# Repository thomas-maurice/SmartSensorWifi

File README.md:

# Smart Sensor WiFi
## General information

 * Developpement status : *work in progress*
 * Project version   : 0.1 alpha

Project led by:

 * Thomas Maurice <Thomas.Maurice@polytech-lille.net>
 * Benoit Maliar  <Benoit.Maliar@polytech-lille.net>

## About the project
This project aims to build a network of sensors which can easily be
deployed into any building to monitor it. The sensors would be able to
monitor temperature, light, moist, presence and so on and send everything
to a centralized database into which data will be stored and processed.

We can easily imagine which use can be done of this kind of sensor networks
in the field of energy-efficient building.

For now, this project is part of a student project led by Polytech'Lille,
a french school of engineering.

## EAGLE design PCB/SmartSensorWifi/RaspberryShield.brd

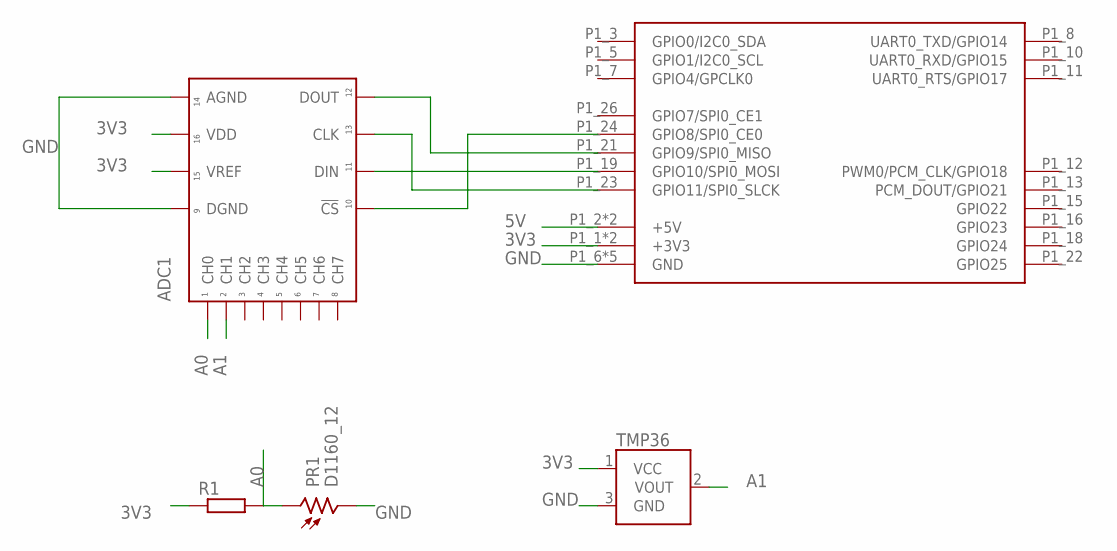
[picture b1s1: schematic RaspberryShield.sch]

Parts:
ADC1: 21298EDIP; DIP16
PR1: D1160_12; D11XX
R1: R-EU_0207/7; 0207/7
TMP36: TMP36GT9; TO-92
U$1: RPI-B-V1SHIELD; RPI-B-V1-SHIELD

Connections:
3V3: ADC1.P$15 (VREF), ADC1.P$16 (VDD), R1.1, TMP36.1 (VCC), U$1.P1_1 (+3V3), U$1.P1_17 (+3V3)
5V: U$1.P1_2 (+5V), U$1.P1_4 (+5V)
A0: ADC1.P$1 (CH0), PR1.1, R1.2
A1: ADC1.P$2 (CH1), TMP36.2 (VOUT)
GND: ADC1.P$9 (DGND), ADC1.P$14 (AGND), PR1.2, TMP36.3 (GND), U$1.P1_6 (GND), U$1.P1_9 (GND), U$1.P1_14 (GND), U$1.P1_20 (GND), U$1.P1_25 (GND)
unnamed: ADC1.P$12 (DOUT), U$1.P1_21 (GPIO9/SPI0_MISO)
unnamed: ADC1.P$11 (DIN), U$1.P1_19 (GPIO10/SPI0_MOSI)
unnamed: ADC1.P$13 (CLK), U$1.P1_23 (GPIO11/SPI0_SLCK)
unnamed: ADC1.P$10 (!CS), U$1.P1_24 (GPIO8/SPI0_CE0)

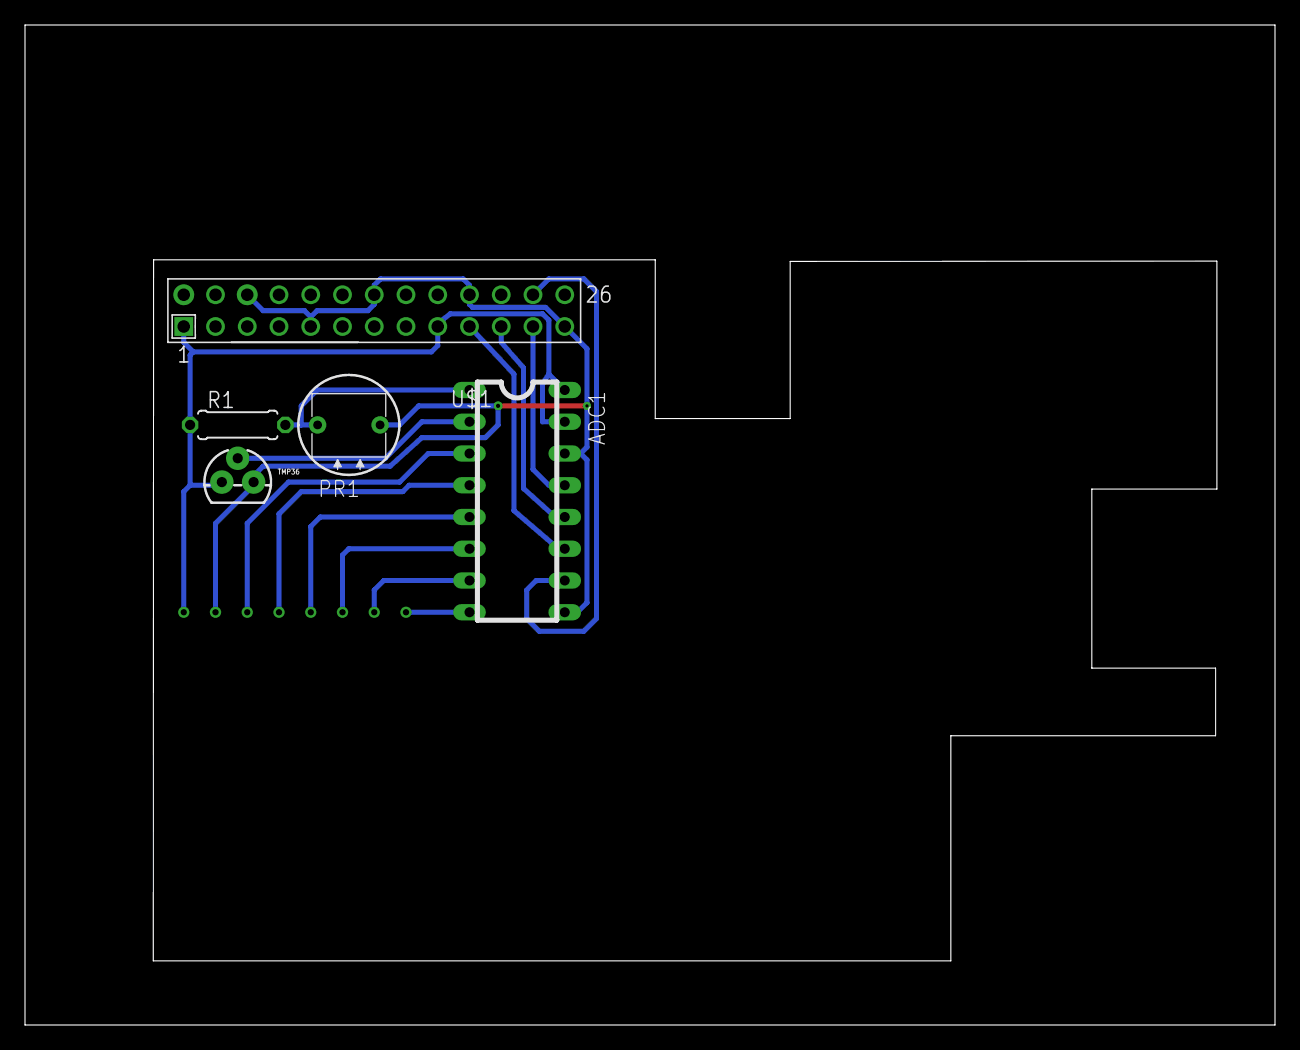
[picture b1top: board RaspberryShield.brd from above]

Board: 2 copper layers, 100.0 x 80.0 mm, 5 parts (0 on the bottom side), 9 nets.

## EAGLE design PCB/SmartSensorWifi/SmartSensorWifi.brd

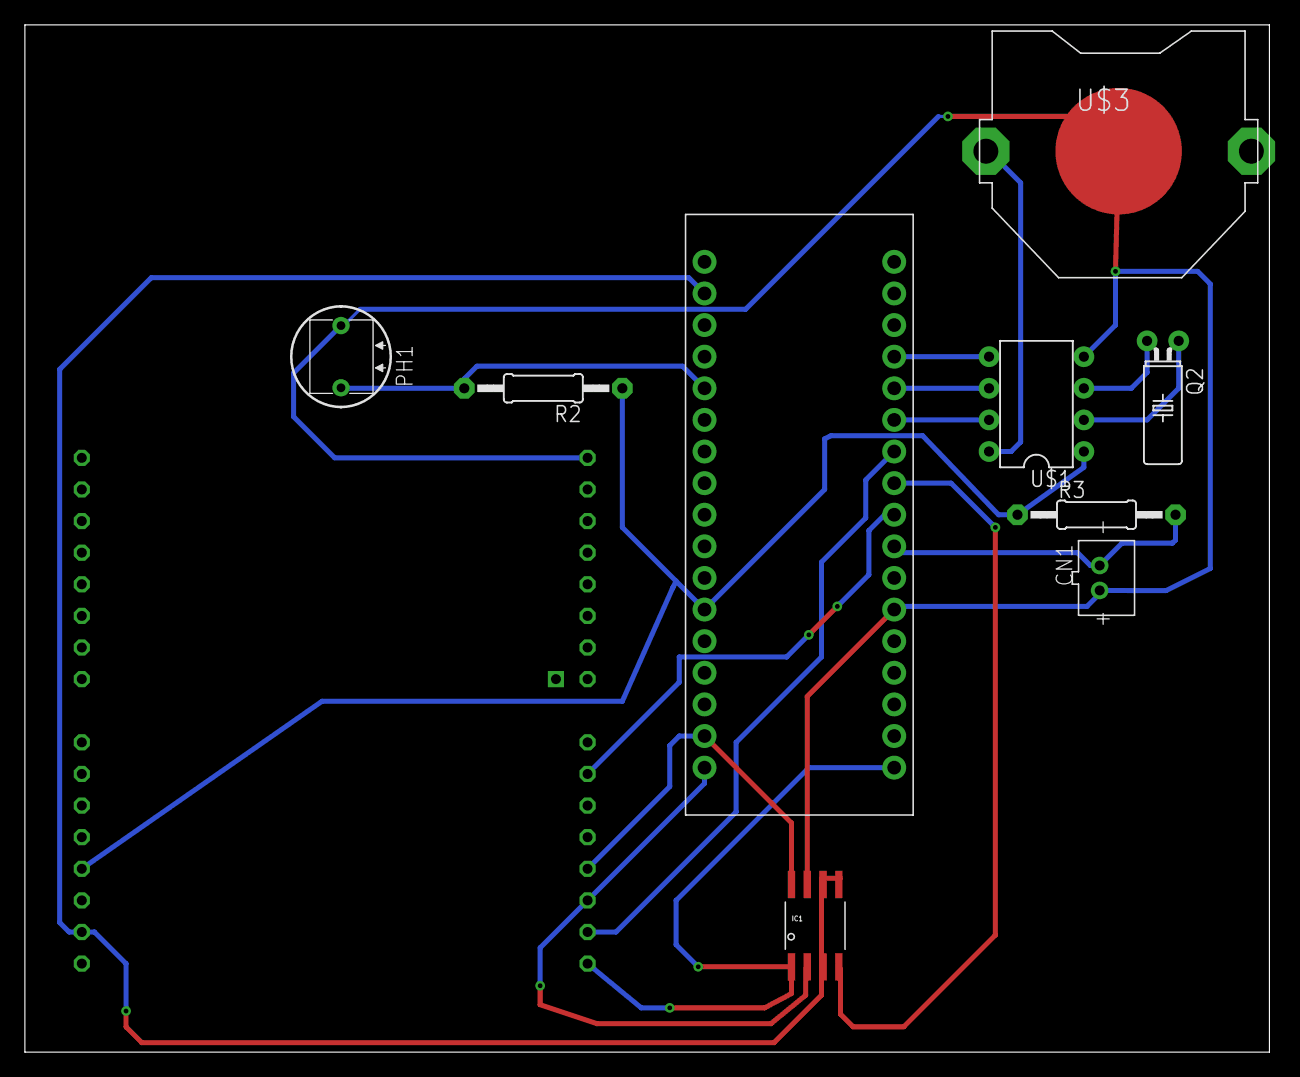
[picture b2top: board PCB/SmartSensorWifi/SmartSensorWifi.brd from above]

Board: 2 copper layers, 100.0 x 82.5 mm, 10 parts (1 on the bottom side), 18 nets.

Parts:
CN1: JST-PH-2-THM
IC1: AT45DB-S; SOIC8_208MIL
PH1: D1160_12; D11XX
Q2: TC38H
R2: 220; 0207/12
R3: 0207/12
U$1: DS1302; DIL08-ROUND
U$2: ARDUINOMICRO
U$3: CR2032-THRU
U$4: WIZFISTACKED; WIZFI210STACKABLE

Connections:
3V3: IC1.3, U$2.P$33, U$4.VIN3V3
5V: R2.1, R3.1, U$1.1, U$2.P$23, U$4.VDDIO
A1: PH1.1, R2.2, U$2.P$30
CS_FLASH: IC1.4, U$2.P$8
CS_WIFI: U$2.P$7, U$4.SPI_CS
GND: CN1.1, IC1.7, U$1.4, U$2.P$21, U$3.-
MISO: IC1.8, U$2.P$19, U$4.SPI_MISO
MOSI: IC1.1, U$2.P$17, U$4.SPI_MOSI
unnamed: U$1.5, U$2.P$4
unnamed: Q2.2, U$1.3
unnamed: Q2.1, U$1.2
unnamed: U$1.7, U$2.P$6
unnamed: U$1.6, U$2.P$5
unnamed: U$1.8, U$3.+1
PSHBTN: CN1.2, R3.2, U$2.P$10
S$1: PH1.2, U$4.GND
SCK: IC1.2, U$2.P$18, U$4.SPI_CLK
WIFI_HOSTWAKEUP: U$2.P$9, U$4.GPIO19

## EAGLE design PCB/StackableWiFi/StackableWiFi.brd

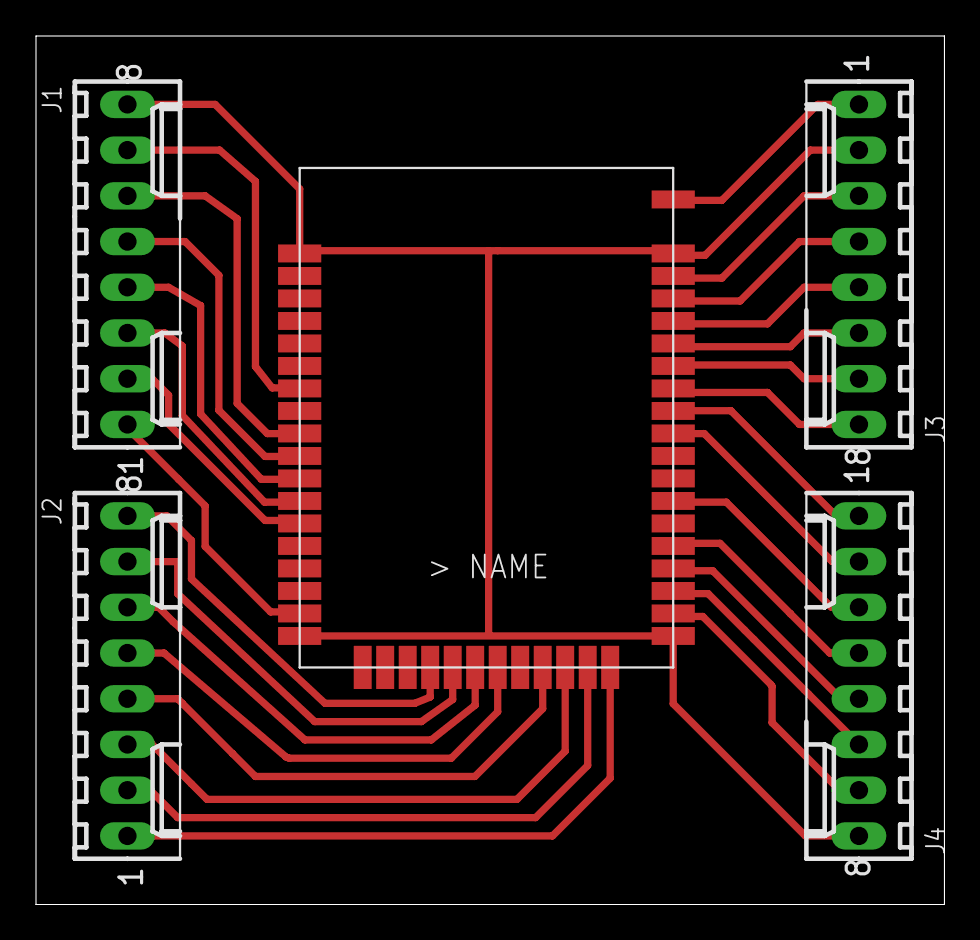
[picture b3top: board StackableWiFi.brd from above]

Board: 2 copper layers, 50.5 x 48.2 mm, 5 parts (0 on the bottom side), 32 nets.

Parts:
J1, J2, J3, J4: 22-27-2081-08; 6410-08
WIFI1: WIZFI210

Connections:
unnamed: J1.8, WIFI1.1
unnamed: J1.7, WIFI1.7
unnamed: J1.6, WIFI1.9
unnamed: J1.5, WIFI1.10
unnamed: J1.4, WIFI1.11
unnamed: J1.3, WIFI1.12
unnamed: J1.2, WIFI1.13
unnamed: J1.1, WIFI1.17
unnamed: J4.8, WIFI1.18, WIFI1.31
unnamed: J2.8, WIFI1.22
unnamed: J2.7, WIFI1.23
unnamed: J2.6, WIFI1.24
unnamed: J2.5, WIFI1.25
unnamed: J2.4, WIFI1.27
unnamed: J2.3, WIFI1.28
unnamed: J2.2, WIFI1.29
unnamed: J2.1, WIFI1.30
unnamed: J4.7, WIFI1.32
unnamed: J4.6, WIFI1.33
unnamed: J4.5, WIFI1.34
unnamed: J4.4, WIFI1.35
unnamed: J4.3, WIFI1.37
unnamed: J4.2, WIFI1.40
unnamed: J4.1, WIFI1.41
unnamed: J3.8, WIFI1.42
unnamed: J3.7, WIFI1.43
unnamed: J3.6, WIFI1.44
unnamed: J3.5, WIFI1.45
unnamed: J3.4, WIFI1.46
unnamed: J3.3, WIFI1.47
unnamed: J3.2, WIFI1.48
unnamed: J3.1, WIFI1.49

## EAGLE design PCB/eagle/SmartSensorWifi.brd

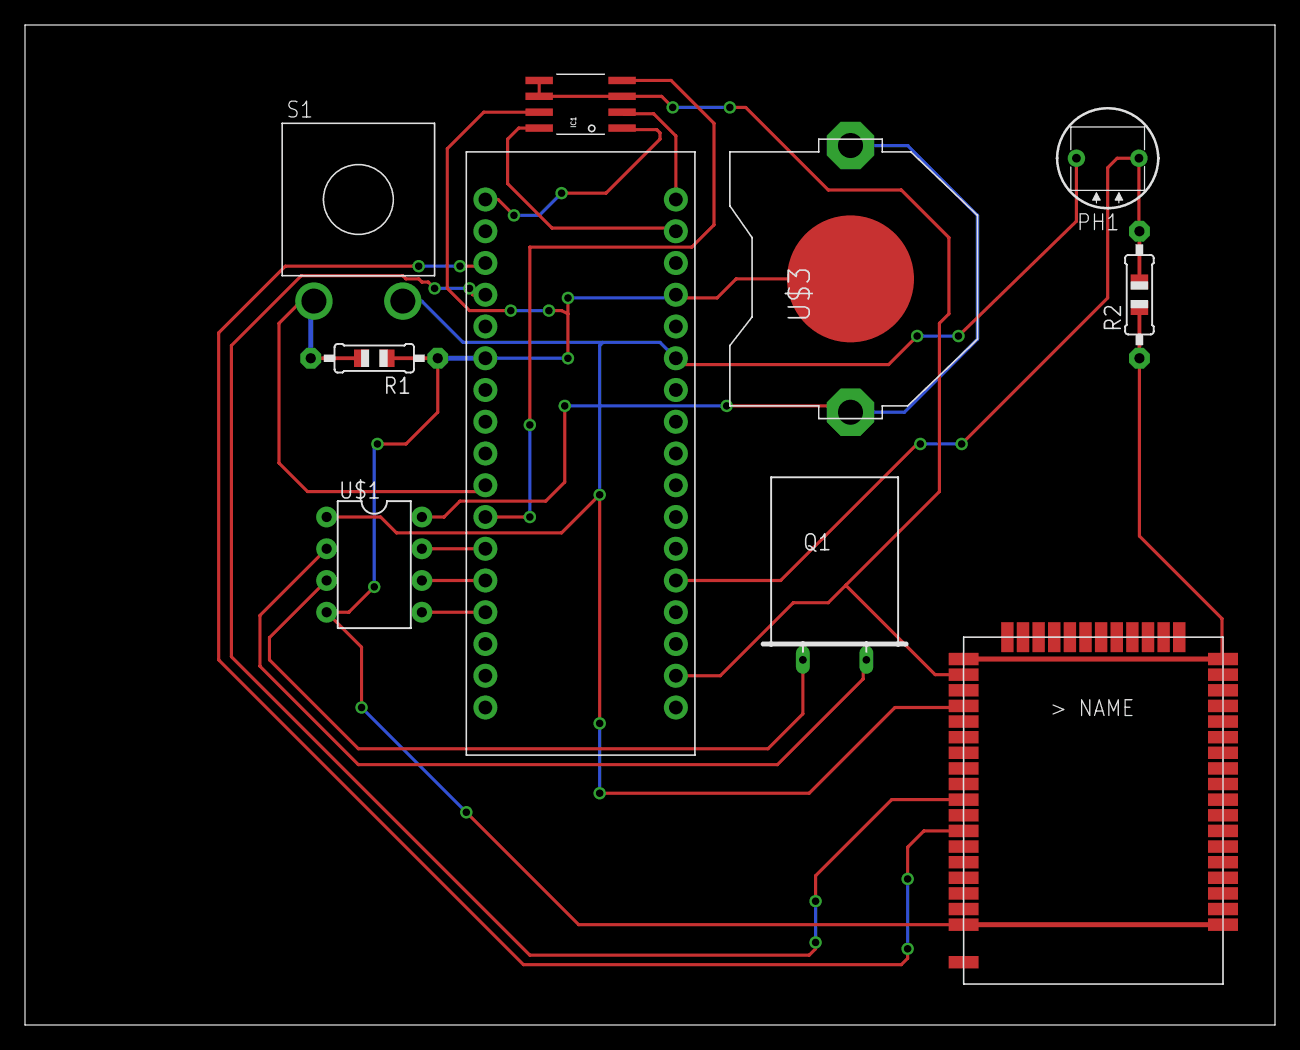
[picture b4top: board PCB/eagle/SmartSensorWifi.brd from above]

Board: 2 copper layers, 100.0 x 80.0 mm, 10 parts (0 on the bottom side), 17 nets.

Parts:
IC1: AT45DB-S; SOIC8_208MIL
PH1: D1160_12; D11XX
Q1: Q
R1, R2: 0805-THM
S1: SPST; JUDCOSPST
U$1: DS1302; DIL08-ROUND
U$2: ARDUINOMICRO
U$3: CR2032-THRU
WIFI1: WIZFI210

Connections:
GND: IC1.7, R1.1, R2.1, U$1.4, U$2.P$12, U$2.P$21, U$3.-, WIFI1.1, WIFI1.18, WIFI1.31, WIFI1.48
unnamed: U$1.5, U$2.P$4
unnamed: Q1.1, U$1.3
unnamed: Q1.2, U$1.2
unnamed: U$1.7, U$2.P$6
unnamed: U$1.6, U$2.P$5
unnamed: IC1.8, U$2.P$19
unnamed: IC1.2, U$2.P$18
unnamed: IC1.1, U$2.P$17
unnamed: IC1.3, IC1.5, IC1.6, U$2.P$33, WIFI1.32
unnamed: U$1.8, U$3.+1, U$3.+2
unnamed: IC1.4, U$2.P$7
unnamed: R1.2, S1.T, U$2.P$8
unnamed: U$2.P$14, WIFI1.40
unnamed: U$2.P$15, WIFI1.42
unnamed: PH1.2, R2.2, U$2.P$30
VCC: PH1.1, S1.P, U$1.1, U$2.P$23, WIFI1.34

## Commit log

2014-02-02 Creating the repo + adding doc
2014-02-02 Added COPYING
2014-02-02 Added README.md & AUTHORS
2014-02-02 Added compilation script for the documentation
2014-02-03 Ajout des propositions de technologies
2014-02-03 Created README.md
2014-02-06 Added the Arduino part of the project
2014-02-06 Added utility script for the serial port read
2014-02-06 Fixed upload speed to make it work on arduino nano
2014-02-07 Added the eeprom management files + comments and license info
2014-02-08 Added macros
2014-02-08 comments
2014-02-08 Added a README for the util section
2014-02-08 Fixed crash in ASCII mode if non utf8 chars
2014-02-17 Added a lot of documentation
2014-02-18 Added the DS1302 driver
2014-02-19 fixed comments
2014-02-21 Web
    Add the Web folder
2014-02-21 Web
    Add ALL the Web directory
2014-02-28 Added Doxyfile for Doxygen documentation
2014-02-28 Added a README.md
2014-02-28 Enhanced README
2014-02-28 Added PCB folder
2014-02-28 Updated board
2014-02-28 Added auto detection for serial ports
2014-03-05 Added set time/date capabilities
2014-03-06 Updated the eagle files
2014-03-13 Added json test script
2014-03-13 wow much doc
2014-03-13 Updated the PCB/BRD files
2014-03-15 Added the Raspberry SPI soft
2014-03-17 Test Json
2014-03-18 Fonctionnal website
    Adding session (using cookie), captors' adding.
    Partially implemented : delete captors.
2014-03-19 Reconstruction du makefile
2014-03-19 Wow, such captors
    Update index, search, add, del.
2014-03-19 Added wizfi
2014-03-19 Fix search.php
2014-03-24 Search Working !
2014-03-31 Changing Json to Post (recup.php)
2014-04-01 Ability to send post request + report sekeleton
2014-04-02 Adding new functions to administration panel
2014-04-03 Added configurator and the ability to configure the sensor via serial
2014-04-04 Enhanced configurator
2014-04-04 Added doc
2014-04-04 Configurator now works wirelessly
2014-04-07 Update Git with FTP files
2014-04-07 added loads of docs in the microcontroller part
2014-04-07 Start commenting properly yeah !
2014-04-07 Added at commands doc
2014-04-07 THIS IS COMMENTS !
2014-04-07 Adding chart.js in order to make graph
2014-04-07 Commenting the graph's file
2014-04-07 Requests ordered by timestamp
2014-04-08 Created the main files for the report
2014-04-09 Updated configurator
2014-04-09 Fix missing graph when same values
2014-04-09 Fixed master key issue
2014-04-09 added configurator doc
2014-04-10 updated report
2014-04-10 Added accomplishment, sensor, software
2014-04-10 Added accomplishment, sensor, HARDWARE
2014-04-10 added stuff
2014-04-10 Added stuff and skel
2014-04-10 addedshitlolwowsuch
2014-04-10 more shit
2014-04-11 Correction coquille
2014-04-12 Updated doc
2014-04-12 edited configurator
2014-04-12 added report
2014-04-12 enhanced report
2014-04-12 enhanced doc
2014-04-12 Fuck this shit UTF8
2014-04-12 Fix ?
2014-04-12 Acheviements completed !
2014-04-13 Web Completed !
2014-04-13 Conclusion added
2014-04-13 Fixed typos
2014-04-14 Enhanced RaspberrySpi
2014-04-14 Coquilles !
2014-08-31 added untracked files

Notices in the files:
parts and their libraries:
raspberry: This library stands under the CERN Open Hardware Licence.
SparkFun-Sensors: Licensing: Creative Commons ShareAlike 4.0 International - https://creativecommons.org/licenses/by-sa/4.0
